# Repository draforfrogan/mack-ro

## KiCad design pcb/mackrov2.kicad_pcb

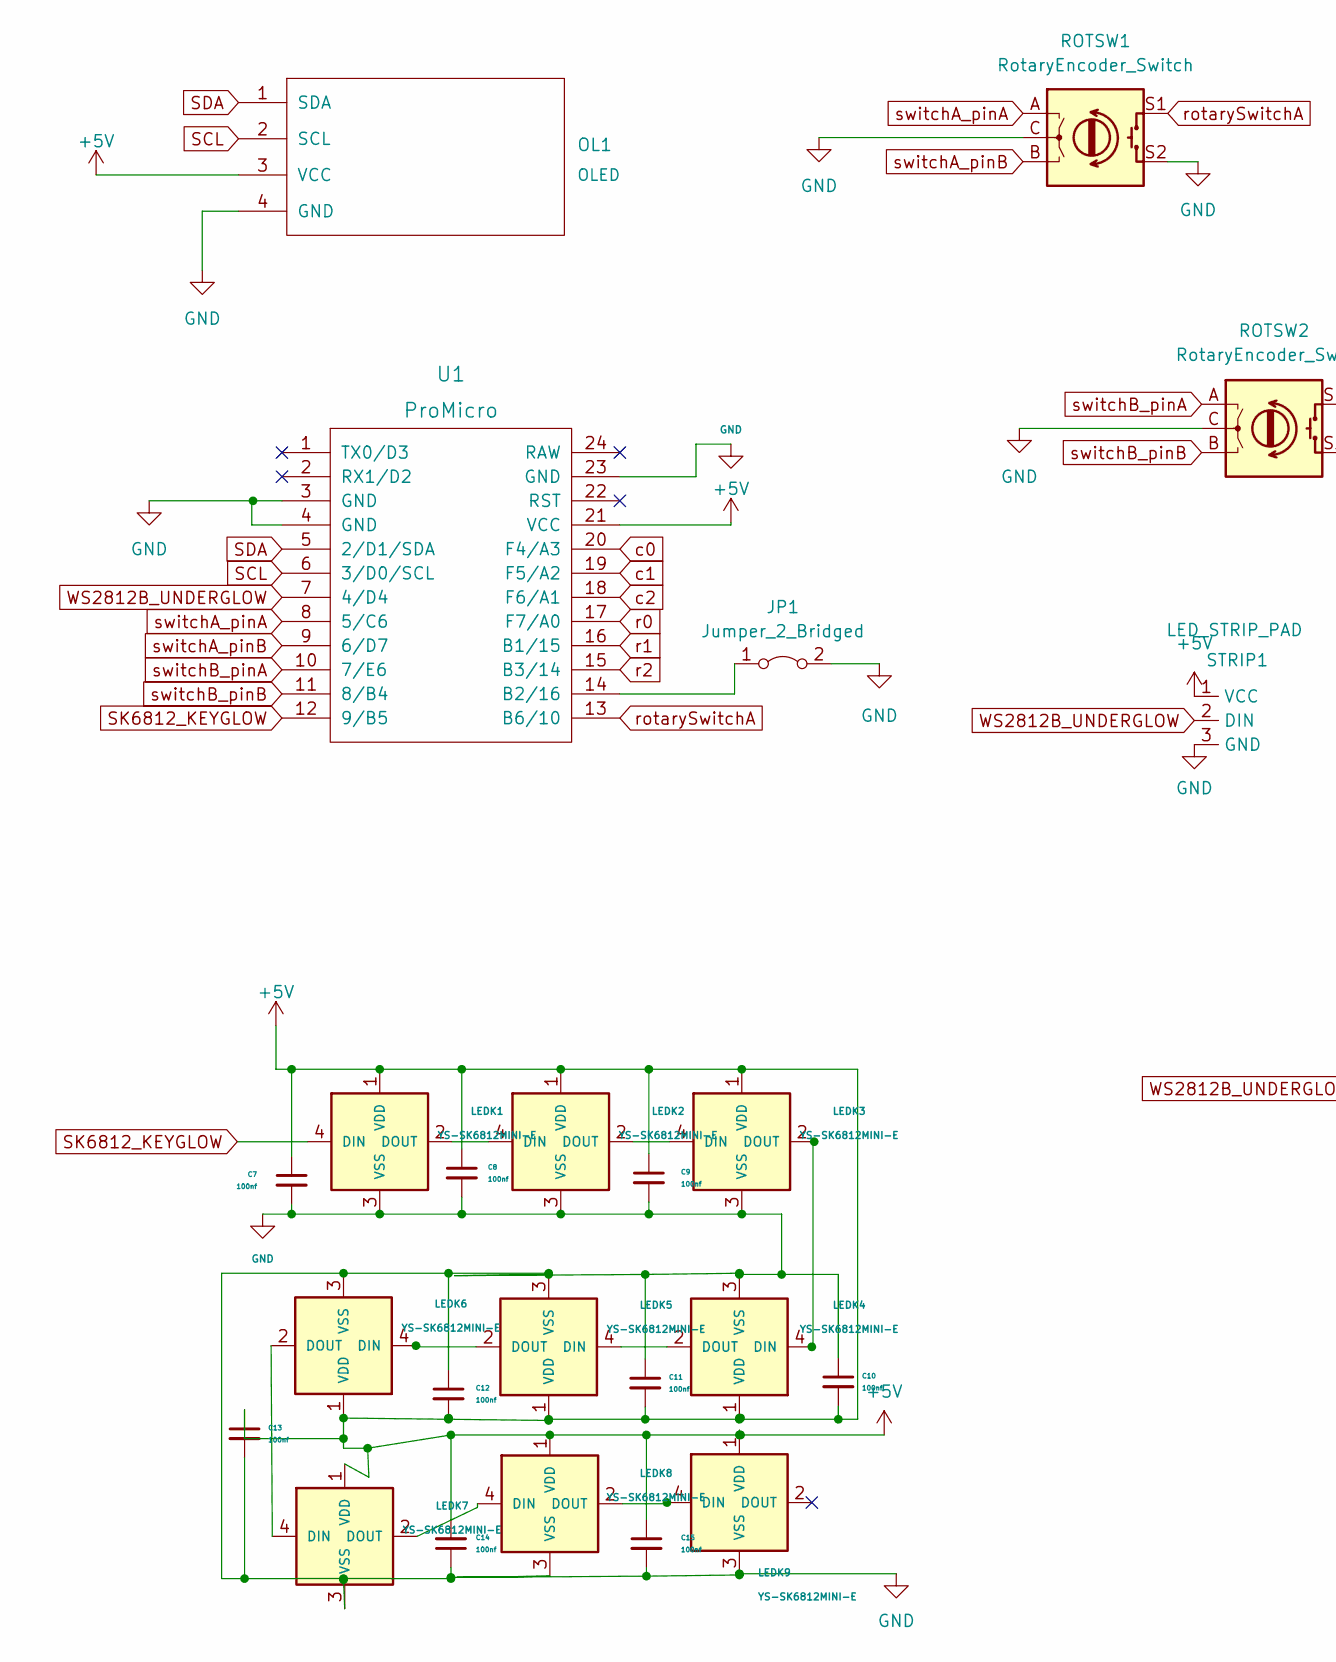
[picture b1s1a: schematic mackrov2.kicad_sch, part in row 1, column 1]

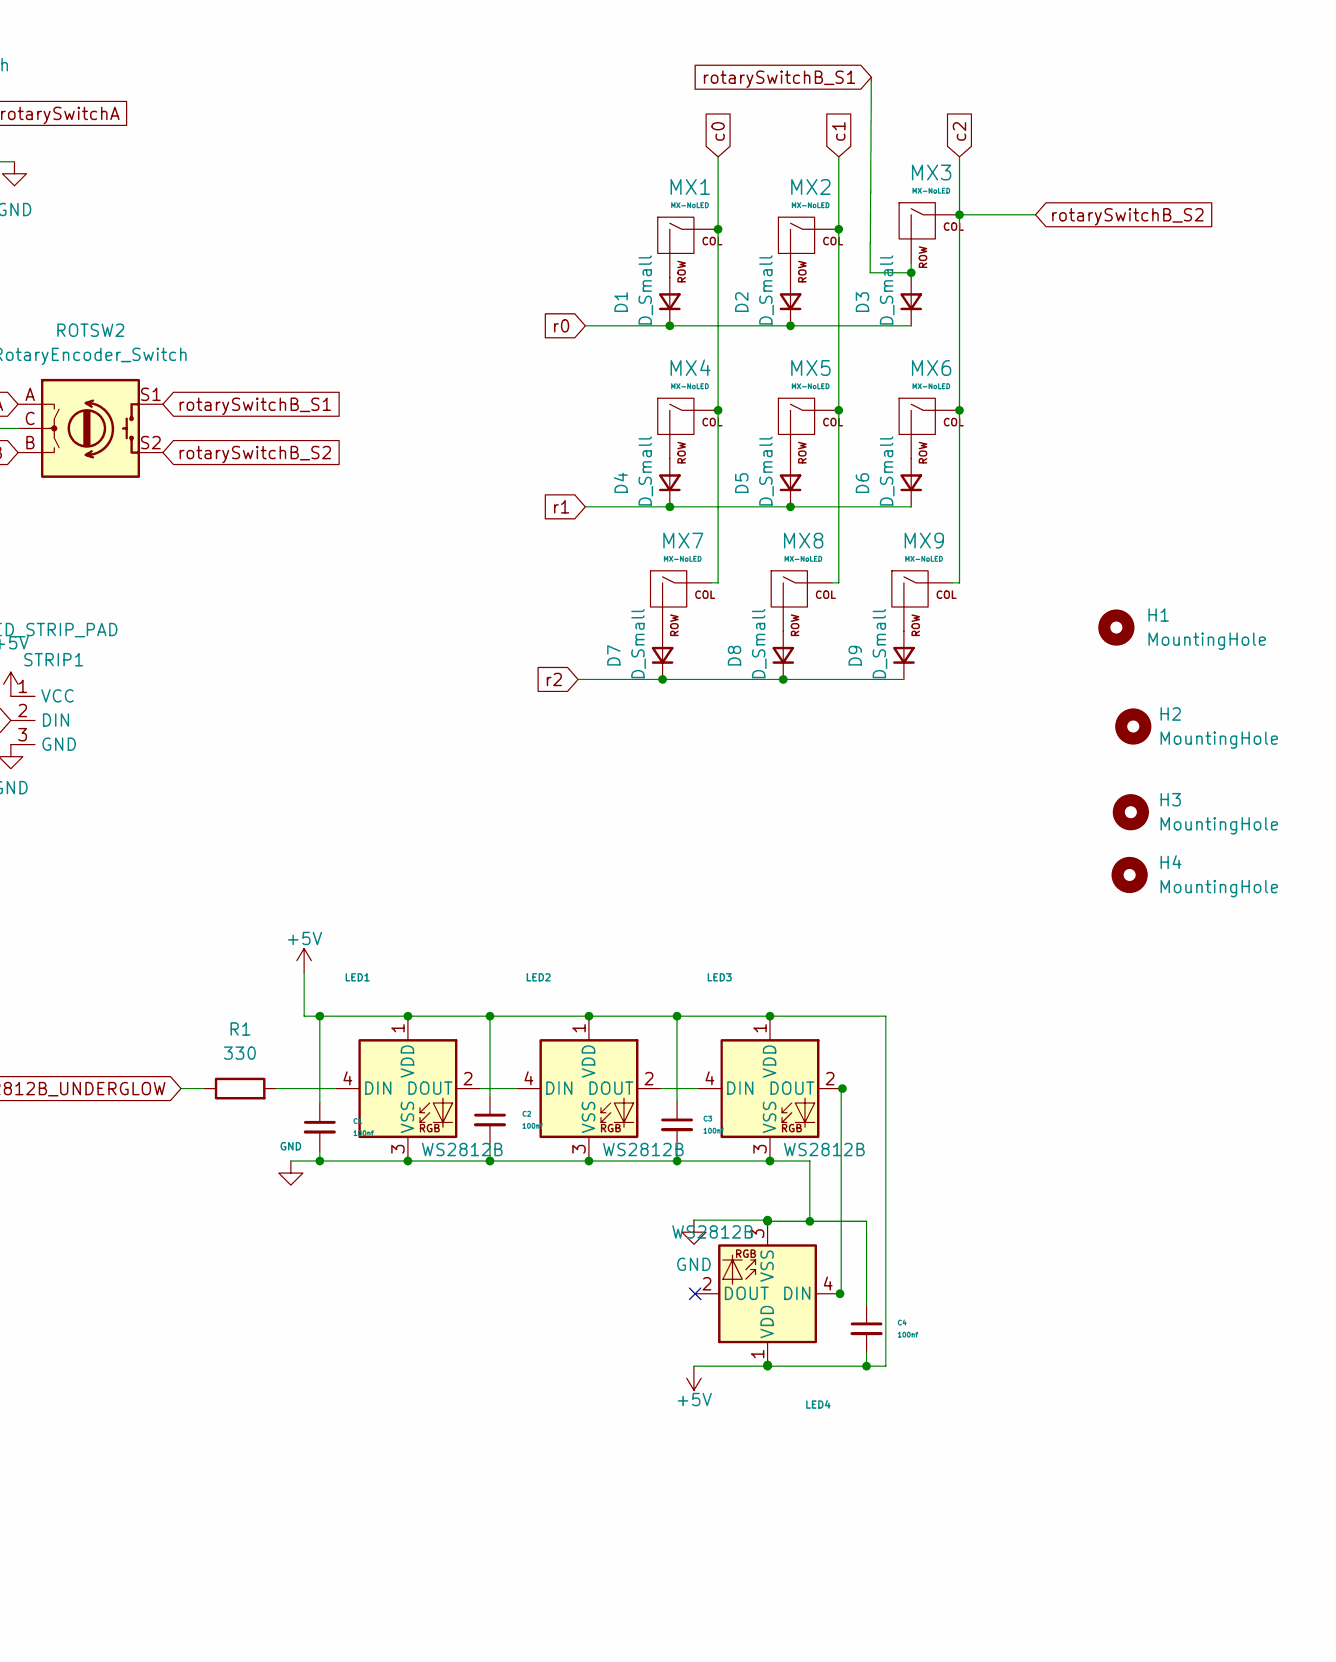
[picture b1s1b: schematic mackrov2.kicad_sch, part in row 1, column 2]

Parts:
C1, C2, C3, C4, C7, C8, C9, C10, C11, C12, C13, C14, C15: 100nf; C_0805_2012Metric_Pad1.18x1.45mm_HandSolder
D1, D2, D3, D4, D5, D6, D7, D8, D9: D_Small; D_0805_2012Metric_Pad1.15x1.40mm_HandSolder
H1, H2, H3, H4: MountingHole; MountingHole_2.2mm_M2_ISO7380
JP1: Jumper_2_Bridged; SolderJumper-2_P1.3mm_Open_Pad1.0x1.5mm
LED1, LED2, LED3, LED4: WS2812B; LED_WS2812B_PLCC4_5.0x5.0mm_P3.2mm
LEDK1, LEDK2, LEDK3, LEDK4, LEDK5, LEDK6, LEDK7, LEDK8, LEDK9: YS-SK6812MINI-E
MX1, MX2, MX3, MX4, MX5, MX6, MX7, MX8, MX9: MX-NoLED; CherryMX_Hotswap
OL1: OLED; OLED_v2
R1: 330; R_0805_2012Metric_Pad1.20x1.40mm_HandSolder
ROTSW1: RotaryEncoder_Switch; RotaryEncoder_Alps_EC11E-Switch_Vertical_H20mm
ROTSW2: RotaryEncoder_Switch; RotaryEncoder_Alps_EC11E-Switch_Vertical_H20mm_CircularMoun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
STRIP1: LED_STRIP_PAD; StripLED_1side
U1: ProMicro; ProMicro_v3.5

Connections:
+5V: C1.1, C2.1, C3.1, C4.2, C7.1, C8.1, C9.1, C10.2, C11.2, C12.2, C13.1, C14.2, C15.1, LED1.1 (VDD), LED2.1 (VDD), LED3.1 (VDD), LED4.1 (VDD), LEDK1.1 (VDD), LEDK2.1 (VDD), LEDK3.1 (VDD), LEDK4.1 (VDD), LEDK5.1 (VDD), LEDK6.1 (VDD), LEDK7.1 (VDD), LEDK8.1 (VDD), LEDK9.1 (VDD), OL1.3 (VCC), STRIP1.1 (VCC), U1.21 (VCC)
GND: C1.2, C2.2, C3.2, C4.1, C7.2, C8.2, C9.2, C10.1, C11.1, C12.1, C13.2, C14.1, C15.2, JP1.2 (B), LED1.3 (VSS), LED2.3 (VSS), LED3.3 (VSS), LED4.3 (VSS), LEDK1.3 (VSS), LEDK2.3 (VSS), LEDK3.3 (VSS), LEDK4.3 (VSS), LEDK5.3 (VSS), LEDK6.3 (VSS), LEDK7.3 (VSS), LEDK8.3 (VSS), LEDK9.3 (VSS), OL1.4 (GND), ROTSW1.C, ROTSW1.S2, ROTSW2.C, STRIP1.3 (GND), U1.4 (GND), U1.23 (GND)
unnamed: D1.2 (A), MX1.2 (ROW)
unnamed: D2.2 (A), MX2.2 (ROW)
unnamed: D4.2 (A), MX4.2 (ROW)
unnamed: D5.2 (A), MX5.2 (ROW)
unnamed: D6.2 (A), MX6.2 (ROW)
unnamed: D7.2 (A), MX7.2 (ROW)
unnamed: D8.2 (A), MX8.2 (ROW)
unnamed: D9.2 (A), MX9.2 (ROW)
unnamed: JP1.1 (A), U1.14 (B2/16)
unnamed: LED1.2 (DOUT), LED2.4 (DIN)
unnamed: LED1.4 (DIN), R1.2
unnamed: LED2.2 (DOUT), LED3.4 (DIN)
unnamed: LED3.2 (DOUT), LED4.4 (DIN)
unnamed: LEDK1.2 (DOUT), LEDK2.4 (DIN)
unnamed: LEDK2.2 (DOUT), LEDK3.4 (DIN)
unnamed: LEDK3.2 (DOUT), LEDK4.4 (DIN)
unnamed: LEDK4.2 (DOUT), LEDK5.4 (DIN)
unnamed: LEDK5.2 (DOUT), LEDK6.4 (DIN)
unnamed: LEDK6.2 (DOUT), LEDK7.4 (DIN)
unnamed: LEDK7.2 (DOUT), LEDK8.4 (DIN)
unnamed: LEDK8.2 (DOUT), LEDK9.4 (DIN)
SCL: OL1.2 (SCL), U1.6 (3/D0/SCL)
SDA: OL1.1 (SDA), U1.5 (2/D1/SDA)
SK6812_KEYGLOW: LEDK1.4 (DIN), U1.12 (9/B5)
WS2812B_UNDERGLOW: R1.1, STRIP1.2 (DIN), U1.7 (4/D4)
c0: MX1.1 (COL), MX4.1 (COL), MX7.1 (COL), U1.20 (F4/A3)
c1: MX2.1 (COL), MX5.1 (COL), MX8.1 (COL), U1.19 (F5/A2)
c2: MX3.1 (COL), MX6.1 (COL), MX9.1 (COL), ROTSW2.S2, U1.18 (F6/A1)
r0: D1.1 (K), D2.1 (K), D3.1 (K), U1.17 (F7/A0)
r1: D4.1 (K), D5.1 (K), D6.1 (K), U1.16 (B1/15)
r2: D7.1 (K), D8.1 (K), D9.1 (K), U1.15 (B3/14)
rotarySwitchA: ROTSW1.S1, U1.13 (B6/10)
rotarySwitchB_S1: D3.2 (A), MX3.2 (ROW), ROTSW2.S1
switchA_pinA: ROTSW1.A, U1.8 (5/C6)
switchA_pinB: ROTSW1.B, U1.9 (6/D7)
switchB_pinA: ROTSW2.A, U1.10 (7/E6)
switchB_pinB: ROTSW2.B, U1.11 (8/B4)

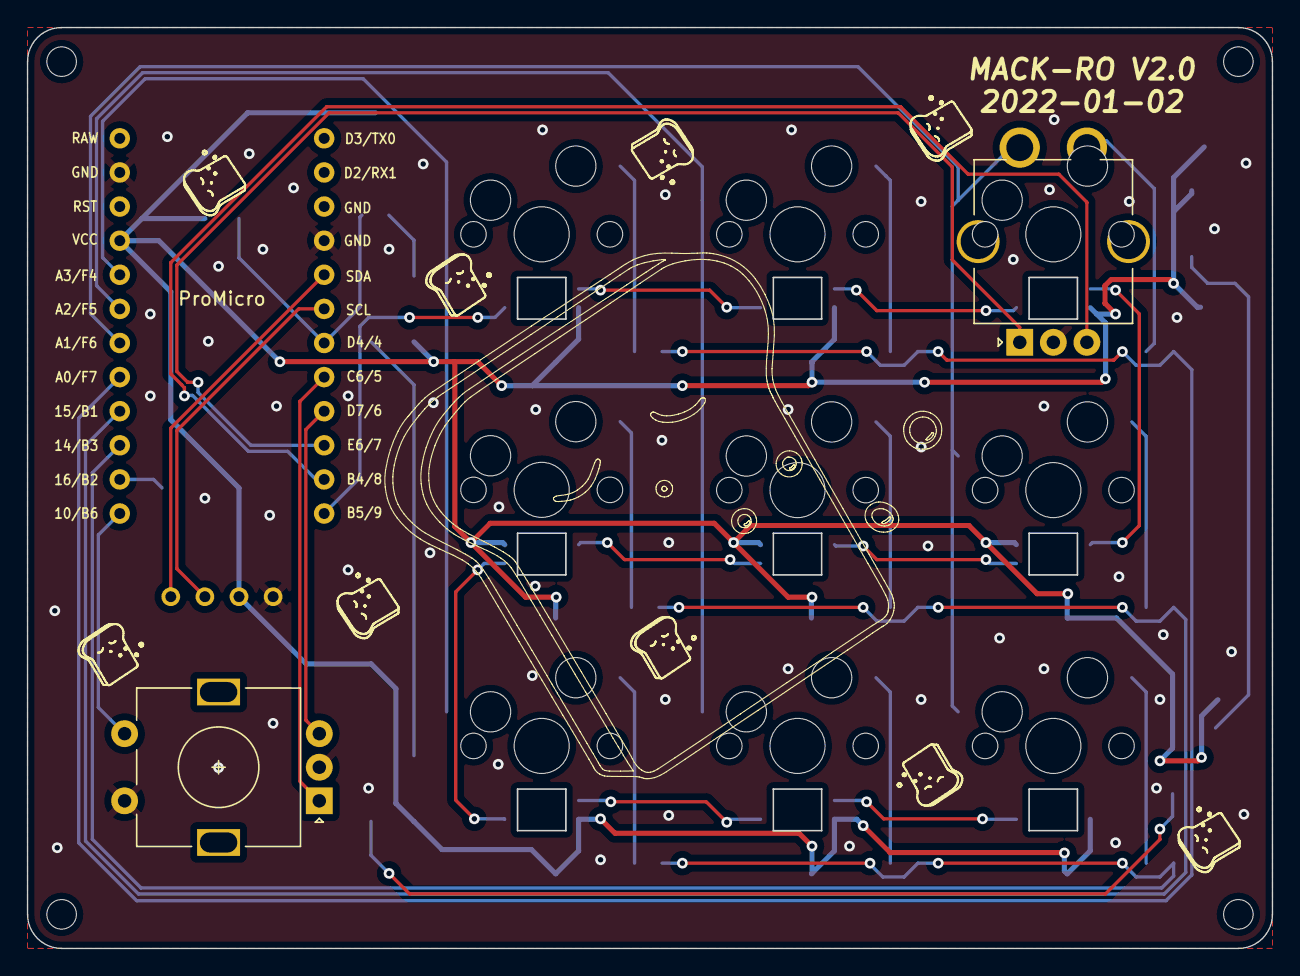
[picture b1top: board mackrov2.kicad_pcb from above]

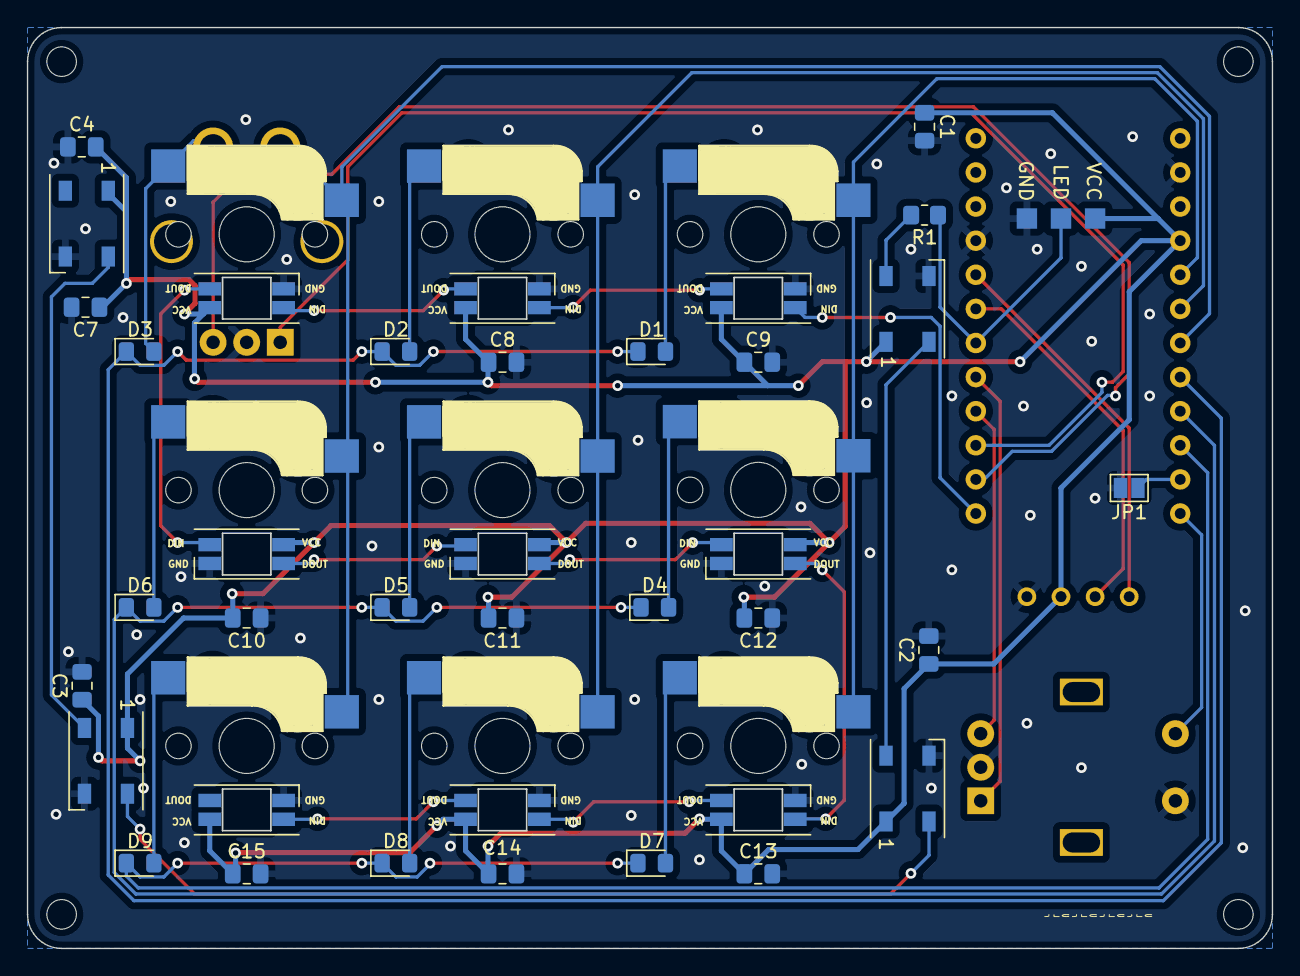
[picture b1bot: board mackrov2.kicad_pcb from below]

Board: 2 copper layers, 92.7 x 68.6 mm, 55 parts (38 on the bottom side), 39 nets.

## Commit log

2022-01-03 Add PCB and firmware
